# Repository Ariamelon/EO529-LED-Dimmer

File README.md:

# EO529 LED Dimmer
4-channel 556-based PWM LED dimmer

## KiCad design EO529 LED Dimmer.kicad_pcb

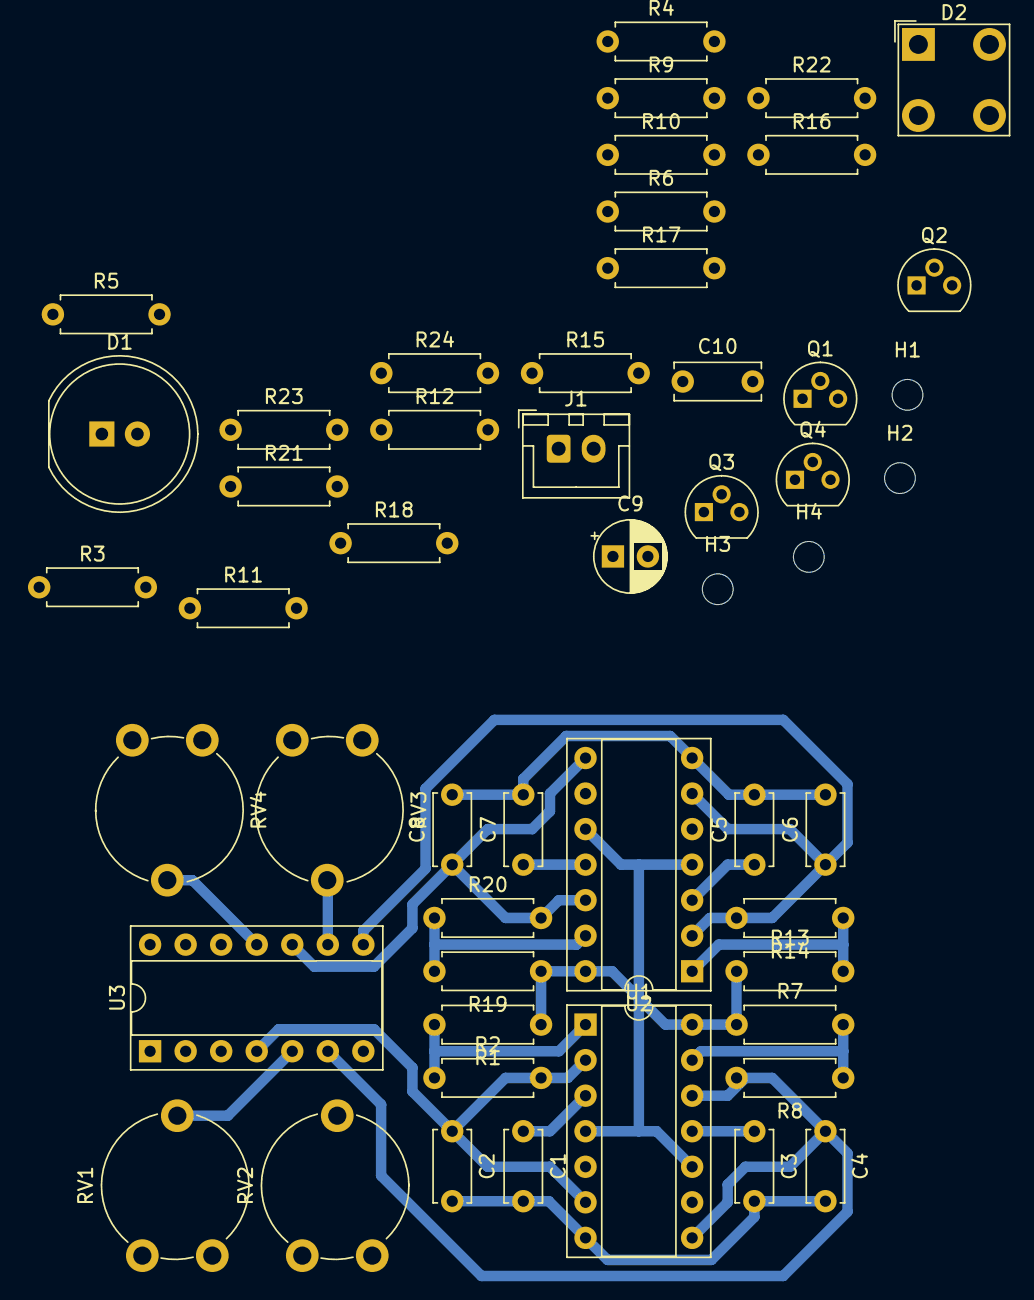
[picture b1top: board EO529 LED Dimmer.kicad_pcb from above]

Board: 2 copper layers, 52 parts (0 on the bottom side), 42 nets.

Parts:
C1, C2, C3, C4, C5, C6, C7, C8: 10n; C_Disc_D5.0mm_W2.5mm_P5.00mm
C9: 10u; CP_Radial_D5.0mm_P2.50mm
C10: 100n; C_Disc_D6.0mm_W2.5mm_P5.00mm
D1: White; LED_D10.0mm
D2: LED_RGBA; LED_BL-FL7680RGB
H1, H2, H3, H4: MountingHole; MountingHole_2.2mm_M2
J1: VBat; JST_XH_B2B-XH-A_1x02_P2.50mm_Vertical
Q1, Q2, Q3, Q4: BC639; TO-92
R1, R2, R7, R8, R13, R14, R19, R20: 10k; R_Axial_DIN0207_L6.3mm_D2.5mm_P7.62mm_Horizontal
R3, R4, R9, R10, R15, R16, R21, R22: 100k; R_Axial_DIN0207_L6.3mm_D2.5mm_P7.62mm_Horizontal
R5, R11, R17, R23: 1k; R_Axial_DIN0207_L6.3mm_D2.5mm_P7.62mm_Horizontal
R6: 150; R_Axial_DIN0207_L6.3mm_D2.5mm_P7.62mm_Horizontal
R12, R24: 220; R_Axial_DIN0207_L6.3mm_D2.5mm_P7.62mm_Horizontal
R18: 180; R_Axial_DIN0207_L6.3mm_D2.5mm_P7.62mm_Horizontal
RV1, RV2, RV3, RV4: 100k; Potentiometer_Piher_PT-10-V10_Vertical
U1, U2: NE556; DIP-14_W7.62mm_Socket
U3: LM339; DIP-14_W7.62mm_Socket

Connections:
Blue: D2.3, R24.2
GND: C1.2, C2.2, C3.2, C4.2, C5.2, C6.2, C7.2, C8.2, C9.2, C10.2, J1.2, Q1.1, Q2.1, Q3.1, Q4.1, R4.2, R10.2, R16.2, R22.2, U1.7, U2.7, U3.12
Green: D2.2, R12.2
unnamed: C1.1, U1.3
unnamed: C2.1, R2.2, U1.2, U1.6, U3.4
unnamed: C3.1, U1.11
unnamed: C4.1, R8.2, U1.8, U1.12, U3.6
unnamed: C5.1, U2.3
unnamed: C6.1, R14.2, U2.2, U2.6, U3.8
unnamed: C7.1, U2.11
unnamed: C8.1, R20.2, U2.8, U2.12, U3.10
unnamed: D1.1, R18.2
unnamed: Q1.2, R6.1
unnamed: Q1.3, R5.1
unnamed: Q2.2, R12.1
unnamed: Q2.3, R11.1
unnamed: Q3.2, R18.1
unnamed: Q3.3, R17.1
unnamed: Q4.2, R24.1
unnamed: Q4.3, R23.1
unnamed: R1.2, R2.1, U1.1
unnamed: R3.2, RV1.3
unnamed: R4.1, RV1.1
unnamed: R5.2, U3.2
unnamed: R7.2, R8.1, U1.13
unnamed: R9.2, RV2.3
unnamed: R10.1, RV2.1
unnamed: R11.2, U3.1
unnamed: R13.2, R14.1, U2.1
unnamed: R15.2, RV3.3
unnamed: R16.1, RV3.1
unnamed: R17.2, U3.14
unnamed: R19.2, R20.1, U2.13
unnamed: R21.2, RV4.3
unnamed: R22.1, RV4.1
unnamed: R23.2, U3.13
unnamed: RV1.2, U3.5
unnamed: RV2.2, U3.7
unnamed: RV3.2, U3.9
unnamed: RV4.2, U3.11
Red: D2.1, R6.2
VCC: C9.1, C10.1, D1.2, D2.4, J1.1, R1.1, R3.1, R7.1, R9.1, R13.1, R15.1, R19.1, R21.1, U1.4, U1.10, U1.14, U2.4, U2.10, U2.14, U3.3

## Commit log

2022-02-17 Revision to circuit
2022-02-18 Fixed broken files
2022-02-19 Updated working design
2022-02-20 Final revision
2022-02-26 New layout, less parts
2022-04-19 -
    -
    -
    -
    -
    -
    -
2022-04-19 Revert "-"
    This reverts commit a00eb99a9a1188f107f06201f65d511c9a46805f.
2022-04-19 Revert "New layout, less parts"
    This reverts commit 43836197f3911cfe2976812753205c060315a555.
2022-04-19 Revert "Final revision"
    This reverts commit 9e4e9cd728e1364b963bc449a0773ff88f127e0e.
2022-04-19 Revert "Updated working design"
    This reverts commit 5c7890285543894d12d83f256540f6246ef53dc3.
2022-04-19 Revert "Fixed broken files"
    This reverts commit e50aa6ede737ee02b3ead64743985b0a59545fc6.
